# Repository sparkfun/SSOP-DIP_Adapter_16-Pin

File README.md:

SSOP DIP Adapter 16-Pin
=======================

[*SparkFun SSOP16 DIP Adapter (BOB-13994)*](https://www.sparkfun.com/products/13994)

This pcb breaks out SSOP16 pin packages to standard 0.1" headers. 

Repository Contents
-------------------

* **/Hardware** - All Eagle design files (.brd, .sch)

Documentation
--------------
* **[Hookup Guide](https://learn.sparkfun.com/tutorials/ssop-16-to-dip-adapter-hookup-guide)** - Basic hookup guide for the adapter board.
* **[SparkFun Fritzing repo](https://github.com/sparkfun/Fritzing_Parts)** - Fritzing diagrams for SparkFun products.
* **[SparkFun 3D Model repo](https://github.com/sparkfun/3D_Models)** - 3D models of SparkFun products. 

License Information
-------------------

This product is _**open source**_! 

Please review the LICENSE.md file for license information. 

If you have any questions or concerns on licensing, please contact techsupport@sparkfun.com.

Distributed as-is; no warranty is given.

- Your friends at SparkFun.

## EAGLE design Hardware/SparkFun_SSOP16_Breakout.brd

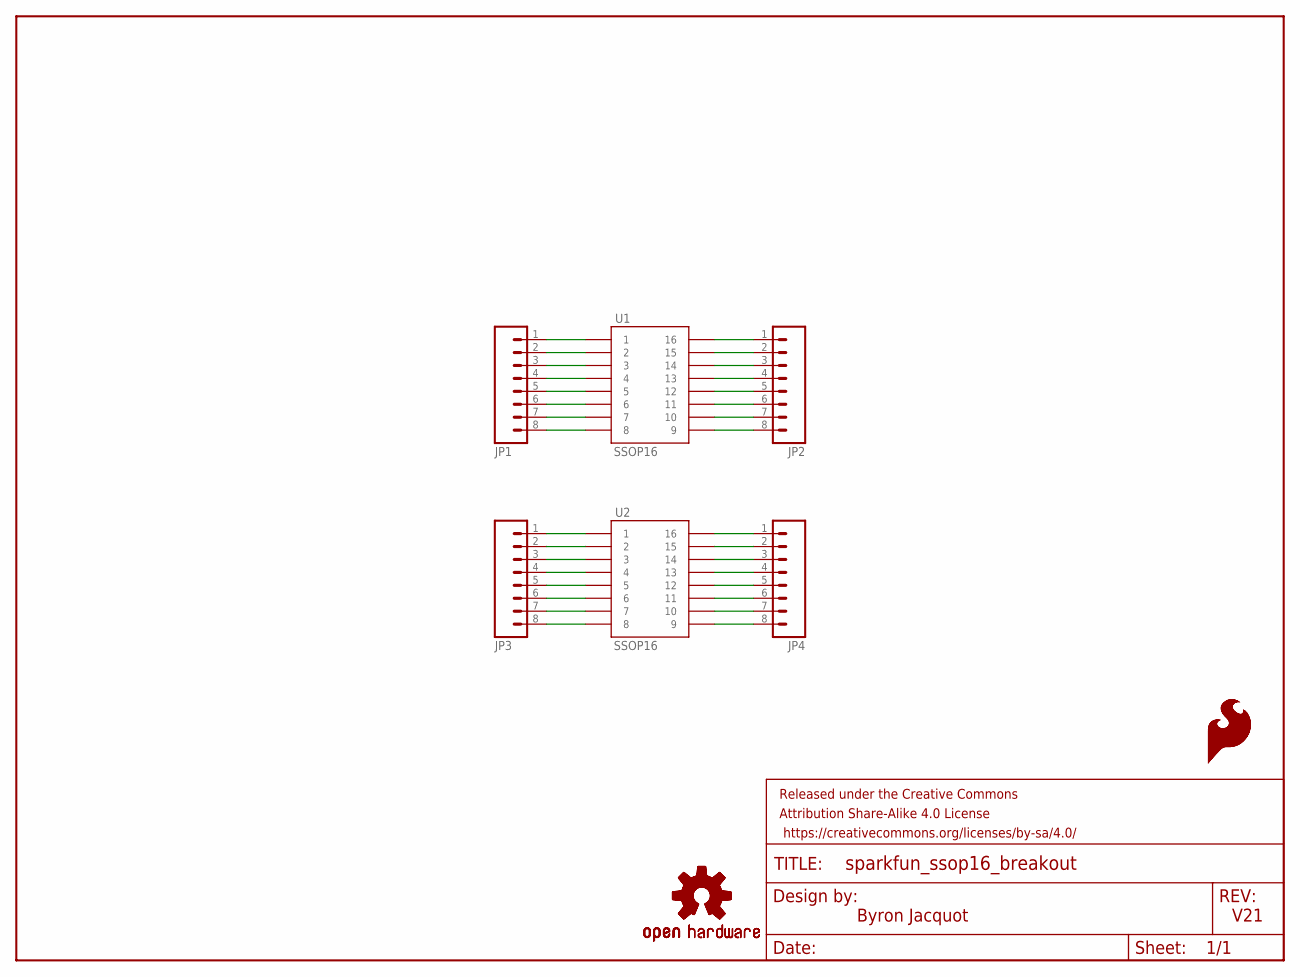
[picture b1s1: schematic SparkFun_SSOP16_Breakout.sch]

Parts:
FRAME1: FRAME-LETTER; CREATIVE_COMMONS
JP1, JP3: M08NO_SILK; 1X08_PIN1_NO_SILK
JP2, JP4: M08NO_SILK_FEMALE_PTH; 1X08_NO_SILK
LOGO1, LOGO2: SFE_LOGO_FLAME.1_INCH; SFE_LOGO_FLAME_.1
LOGO3, LOGO4: OSHW-LOGOS; OSHW-LOGO-S
U1, U2: SSOP16

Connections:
unnamed: JP1.1, U1.P$1 (1)
unnamed: JP1.2, U1.P$2 (2)
unnamed: JP1.3, U1.P$3 (3)
unnamed: JP1.4, U1.P$4 (4)
unnamed: JP1.5, U1.P$5 (5)
unnamed: JP1.6, U1.P$6 (6)
unnamed: JP1.7, U1.P$7 (7)
unnamed: JP1.8, U1.P$8 (8)
unnamed: JP2.1, U1.P$16 (16)
unnamed: JP2.2, U1.P$15 (15)
unnamed: JP2.3, U1.P$14 (14)
unnamed: JP2.4, U1.P$13 (13)
unnamed: JP2.5, U1.P$12 (12)
unnamed: JP2.6, U1.P$11 (11)
unnamed: JP2.7, U1.P$10 (10)
unnamed: JP2.8, U1.P$9 (9)
unnamed: JP4.1, U2.P$16 (16)
unnamed: JP4.2, U2.P$15 (15)
unnamed: JP4.3, U2.P$14 (14)
unnamed: JP4.4, U2.P$13 (13)
unnamed: JP4.5, U2.P$12 (12)
unnamed: JP4.6, U2.P$11 (11)
unnamed: JP4.7, U2.P$10 (10)
unnamed: JP4.8, U2.P$9 (9)
unnamed: JP3.1, U2.P$1 (1)
unnamed: JP3.2, U2.P$2 (2)
unnamed: JP3.3, U2.P$3 (3)
unnamed: JP3.4, U2.P$4 (4)
unnamed: JP3.5, U2.P$5 (5)
unnamed: JP3.6, U2.P$6 (6)
unnamed: JP3.7, U2.P$7 (7)
unnamed: JP3.8, U2.P$8 (8)

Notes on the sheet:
V21
Byron Jacquot

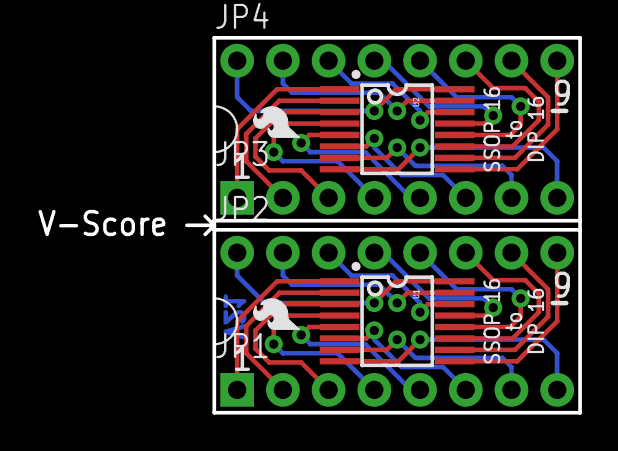
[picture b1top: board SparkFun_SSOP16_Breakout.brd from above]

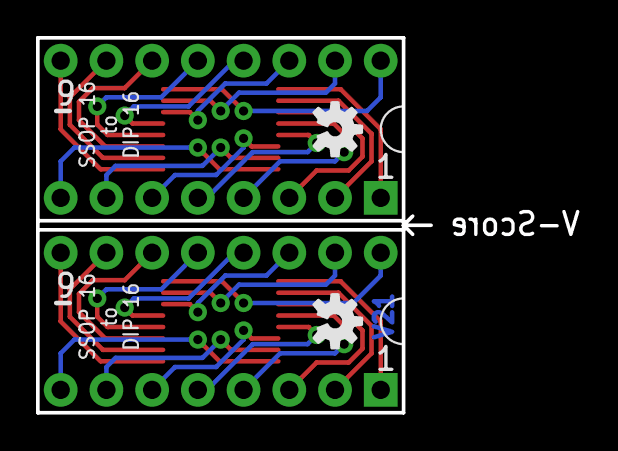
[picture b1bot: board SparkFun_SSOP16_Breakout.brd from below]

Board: 2 copper layers, 30.1 x 20.8 mm, 11 parts (2 on the bottom side), 32 nets.

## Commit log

2015-01-06 Initial hardware commit
2016-07-28 Initial commit of branch files.
2016-07-28 Updated board files
2016-07-29 Moving towards actual design.
    -2-up panel.
    -Dimensioning added.
2016-08-01 Small touch-ups, moving to prototype review.
2016-08-02 Fixes for out-of-order checklist.
2016-08-02 Version number repair
    ...revisions start at V20.
2016-08-09 Changes from group review.
2016-08-09 Handling Eric's checklist issue.
2016-09-27 Moving dimention note to dimension layer.
2016-10-31 Updates after prototypes.
    -Underlines on the pin "9" marks
    -Better centering of board name on bottom silk.
2016-11-03 Checklist updates.
    Package outline to 8 mil.
    Version to V21.
2017-01-20 Updating readme and license with new product info and year

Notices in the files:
parts and their libraries:
SparkFun-Connectors: Licensing: Creative Commons ShareAlike 4.0 International - https://creativecommons.org/licenses/by-sa/4.0
SparkFun-Aesthetics: Released under the Creative Commons Attribution Share-Alike 4.0 License
SparkFun-Aesthetics: https://creativecommons.org/licenses/by-sa/4.0
